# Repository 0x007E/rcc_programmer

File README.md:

# `RCC_programmer` - RCC (UPDI) Programmer

The `RCC_programmer` project is based on a pcb with an [FT230XS](#additional-information) to program the [RCC](https://github.com/0x0007e/rcc) (RGB LED Color Cube). It either can be programmed with the developed module or with a simple self-made [UPDI](#additional-information) converter. The deliverd software writes the defined settings with `avr-dude` over `serialupdi` onto the [ATTiny402](#additional-information).

| Experience | Level |
|:------------|:-----:|
| Soldering   |  |
| Mechanical  |  |
| Software    |  |

# Downloads

| Type      | File               | Description              |
|:---------:|:------------------:|:-------------------------|
| Schematic | [pdf](https://github.com/0x007E/rcc_programmer/releases/latest/download/schematic.pdf) / [cadlab](https://cadlab.io/project/29709/main/files) | Schematic files |
| Board | [pdf](https://github.com/0x007E/rcc_programmer/releases/latest/download/pcb.pdf) / [cadlab](https://cadlab.io/project/29709/main/files) | Board file |
| Drill | [pdf](https://github.com/0x007E/rcc_programmer/releases/latest/download/drill.pdf) | Drill file |
| PCB | [zip](https://github.com/0x007E/rcc_programmer/releases/latest/download/kicad.zip) / [tar](https://github.com/0x007E/rcc_programmer/releases/latest/download/kicad.tar.gz) | KiCAD/Gerber/BoM/Drill files |
| Mechanical | [zip](https://github.com/0x007E/rcc_programmer/releases/latest/download/freecad.zip) / [tar](https://github.com/0x007E/rcc_programmer/releases/latest/download/freecad.tar.gz) | FreeCAD/Housing and PCB (STEP) files     |
| Installer | [exe](https://0x007e.github.io/rcc_programmer/clickonce/setup.exe) | ClickOnce installer (x64) for RCC Programming software |
| Portable | [zip](https://github.com/0x007E/rcc_programmer/releases/latest/download/programmer.zip) / [tar](https://github.com/0x007E/rcc_programmer/releases/latest/download/programmer.tar.gz) | Software (x64) for Programming the RCC |

# Hardware

There are two parts of the hardware. The pcb and the housing of the `RCC_programmer`. The pcb is created with [KiCAD](#additional-information) and the housing with [FreeCAD](#additional-information) . The software is programmed with [Visual Studio](#additional-information). All files are built with `github actions` so that they are ready for a production environment. The housing is printed with a 3D-printer (`Dremel 3D40`) and the software is build as ClickOnce application that can be installed over a simple setup file and keeps automatically up-to-date.

## PCB

The circuit board is populated on one side (Top). The best way for soldering the `SMD` components is within a vapor phase soldering system.

### Top Layer

### Bottom Layer

## Mechanical

The housing has a tolerance of `0.2mm` on each side of the case. So the pcb should fit perfectly in the housing. The tolerance can be modified with `FreeCAD` in the `Parameter` Spreadsheet.

### Assembled

### Exploded

# Programming/Setup

The `RCC_programmer` is powerd over USB with `5V` and uses the internal `3V3` converter of the `FT230XS` as main programming voltage. The programming software itself uses avr-dude in background and a simple [UPDI](#additional-information) circuit to program the `RCC`. It can be programmed over [UPDI](#additional-information) on `TP1`. The firmware for the cube can be downloaded in the [download section](#downloads).

``` bash
#               RCC                     RCC_programmer (Adapter)
#                                     +-------------------------+      +---------------------+
#                                     |          TXD     U  +---+---+  |                     |
#     +---------------------+         |     U     +      S  |  USB  |--+ +-----------------+ |
#     |                     |         |     P    +++     B  +---+---+  | | RCC Programmer  | |
#     |    RCC - Color Cube |         |     D    / \     /      |      | | ~~~~~~~~        | |
#     |                  +--+--+   +--+--+  I    +++     U      |      | | ~~~~~           | |
#     |              VCC | TP3 +---+ VCC |        |      A      |      | | ~~~~~~~~~~~~    | |
#     |              GND | TP2 +---+ GND |  B    +++     R      |      | |                 | |
#     |                  +--+--+   +--+--+  R    | |     T      |      | +-----------------+ |
#     |                     |         |     I    | |            |      |                     |
#     |                  +--+--+   +--+--+  D    +++   +------+ |      | Computer            |
#     |             UPDI | TP1 +---+ PDI +--G-----+    | 3V3  | |      |                     |
#     |                  +--+--+   +--+--+  E    RXD   +------+ |      +---------------------+
#     +---------------------+         +-------------------------+
#
```

# Software

| Icon                                             | Description           |
|:------------------------------------------------:|:----------------------|
|  | ClickOnce installable |

> The app can be installed as clickonce application that automatically gets updated or run as portable app that need to be updated manually. Both files (setup/portable) are found in the [download section](#downloads).

The software loads avr-dude and the current firmware of the `RCC` from predefined repositories in `appsettings.json`. By clicking onto the LEDs the color of each LED can be defined. With the intensity trackbar the brightness of the LEDs can be adjusted. To program the `RCC` the correct selection of the serial port is necessary. By hitting the program button the `RCC` gets programmed over `serialupdi` with `avr-dude` (if the programmer is connected correctly with the `RCC`).

> IMPORTANT: The battery should not be mounted during programming. There will be a short circuit between the internal `3V3` of the `FT230XS` and the battery!!!

# Additional Information

| Type          | Link                                                                 | Description                     |
|:-------------:|:--------------------------------------------------------------------:|:--------------------------------|
| ATtiny402     | [pdf](https://ww1.microchip.com/downloads/en/DeviceDoc/ATtiny202-402-AVR-MCU-with-Core-Independent-Peripherals_and-picoPower-40001969A.pdf) | ATtiny microcontroller |
| FT230XS       | [pdf](https://ftdichip.com/wp-content/uploads/2021/10/DS_FT230X.pdf) | FT230XS Datasheet               |
| UPDI          | [web](https://github.com/0x007e/updi)                                | UPDI-Adapter with AVR-Dude      |
| Visual Studio | [web](https://visualstudio.microsoft.com/)                           | Download page for Visual Studio |
| KiCAD         | [web](https://www.kicad.org/)                                        | KiCAD project page              |
| FreeCAD       | [web](https://www.freecad.org/)                                      | FreeCAD project page            |

---

R. GAECHTER

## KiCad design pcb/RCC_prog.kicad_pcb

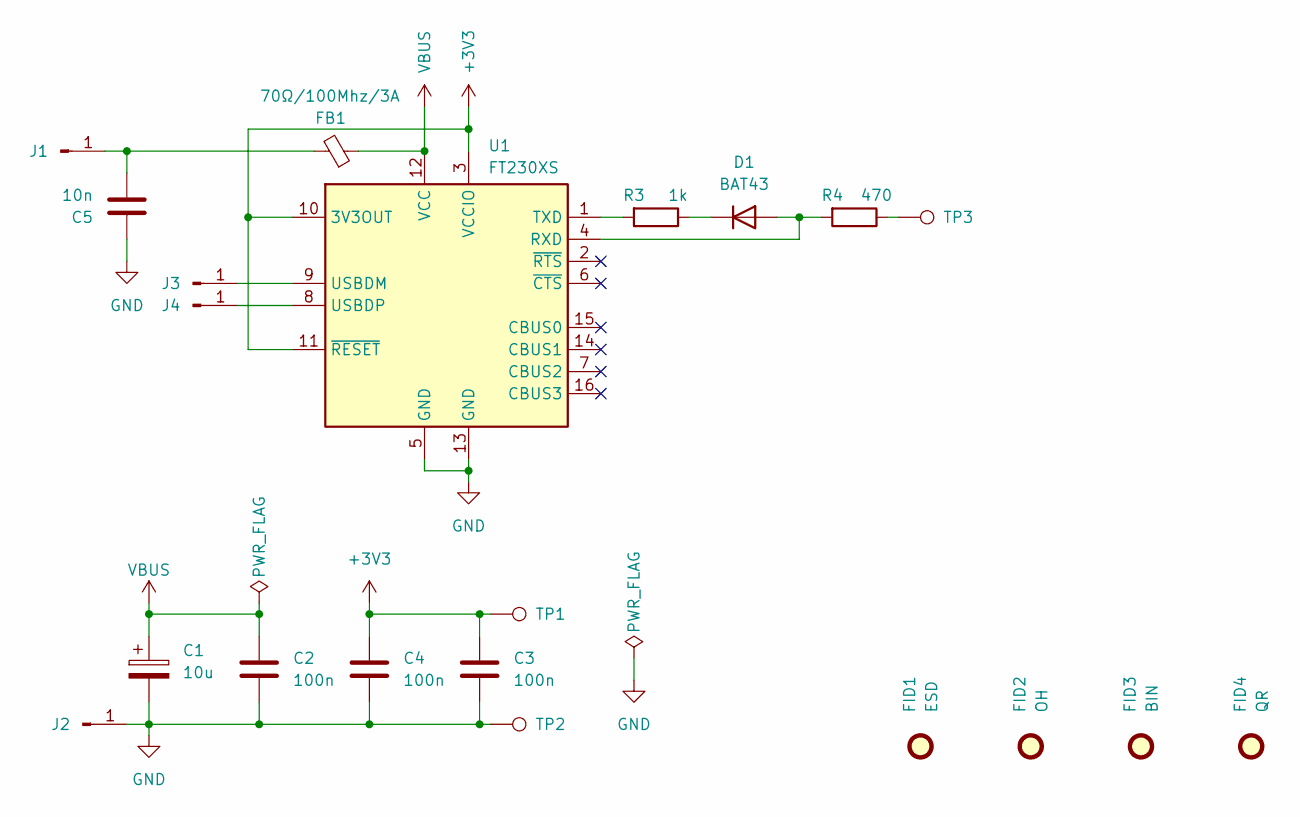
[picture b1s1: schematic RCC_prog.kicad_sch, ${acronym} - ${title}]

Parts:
C1: 10u; CP_EIA-6032-28_Kemet-C
C2, C3, C4: 100n; C_1206_3216Metric
C5: 10n; C_1206_3216Metric
D1: BAT43; D_MiniMELF
FB1: 70Ω/100Mhz/3A; L_1206_3216Metric
FID1: ESD; ESD-Logo_6.6x6mm_SilkScreen
FID2: OH; OSHW-Logo_5.7x6mm_SilkScreen
FID3: BIN; WEEE-Logo_4.2x6mm_SilkScreen
FID4: QR; QR_0x007e
J1, J2, J3, J4: Conn_01x01_Pin; SolderWire-0.5sqmm_1x01_D0.9mm_OD2.1mm
R3: 1k; R_1206_3216Metric
R4: 470; R_1206_3216Metric
TP1, TP2, TP3: TestPoint; Pogo_Pad_L3.2mm_B2.2mm_D1.75
U1: FT230XS; SSOP-16_3.9x4.9mm_P0.635mm

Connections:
+3V3: C3.2, C4.2, TP1.1, U1.3 (VCCIO), U1.10 (3V3OUT), U1.11 (~RESET)
GND: C1.2, C2.1, C3.1, C4.1, C5.1, J2.1, TP2.1, U1.5 (GND), U1.13 (GND)
unnamed: D1.2 (A), R4.2, U1.4 (RXD)
unnamed: D1.1 (K), R3.1
unnamed: C5.2, FB1.2, J1.1
unnamed: J3.1, U1.9 (USBDM)
unnamed: J4.1, U1.8 (USBDP)
unnamed: R4.1, TP3.1
unnamed: R3.2, U1.1 (TXD)
VBUS: C1.1, C2.2, FB1.1, U1.12 (VCC)

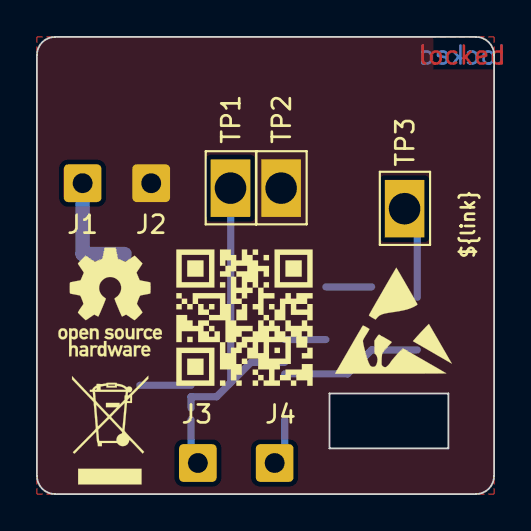
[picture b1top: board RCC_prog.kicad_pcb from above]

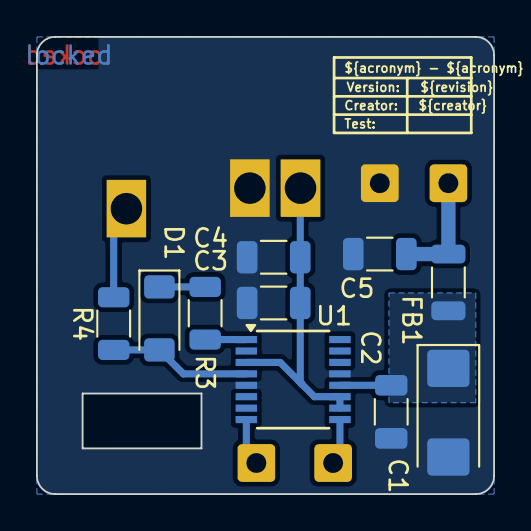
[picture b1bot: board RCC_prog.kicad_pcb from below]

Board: 2 copper layers, 25.4 x 25.4 mm, 21 parts (10 on the bottom side), 10 nets.

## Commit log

2025-10-26 Add splash screen
2025-10-26 Add housing for programmer
2025-10-26 Code refactoring
2025-10-27 Adapt .gitignore
2025-10-27 Add publish profile
2025-10-27 Add build pipeline
2025-10-27 Increase upload-artifact version
2025-10-27 Correct dotnet version
2025-10-27 Add runtime identifier
2025-10-27 Add readytorun property
2025-10-27 Disable bootstrapper
2025-10-27 Remove certfile path from publish xml
2025-10-27 Add certificate import view
2025-10-27 Change certificate fingerprint
2025-10-27 Enable bootstrapper
2025-10-27 Change artefact path
2025-10-27 Remove env variables
2025-10-27 Add release pipeline
2025-10-27 Add clickonce pipeline
2025-10-28 Remove battery from design
2025-10-28 Adapt splash screen graphics
2025-10-28 Remove nullable property
2025-10-28 Remove unused variables
2025-10-28 Add README.md
2025-10-28 Update starting image
2025-10-28 Fix correct upload of artifact
2025-10-28 Fix software link
2025-10-28 Change image text
2025-10-28 Extend software section
2025-10-28 Remove clickonce badge
2025-10-28 Adapt workflow to extended software section
2025-10-28 Fix wrong permission
2025-10-29 Add DeepWiki badge
2025-10-29 Fix typo in programmer icon include
2025-11-06 Optimize cable outlet
2025-11-06 Update cable outlet
2025-11-06 Update splash screen image

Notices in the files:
README.md:
License CC By-NC-SA
License GPLv3
parts and their libraries:
license: CC BY-NC-SA 4.0
